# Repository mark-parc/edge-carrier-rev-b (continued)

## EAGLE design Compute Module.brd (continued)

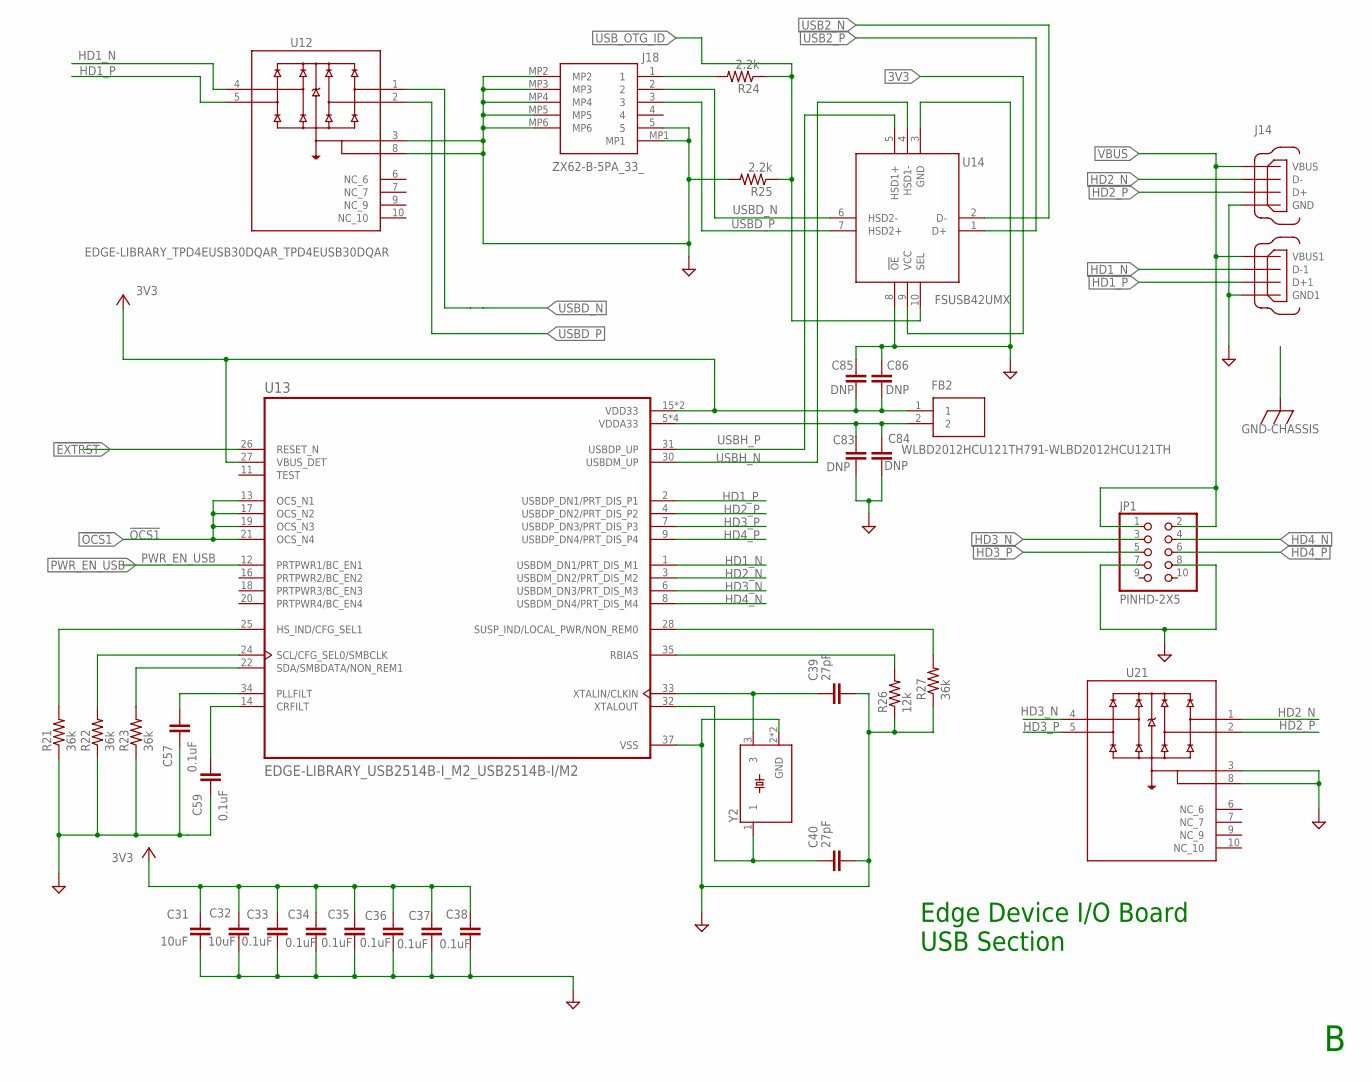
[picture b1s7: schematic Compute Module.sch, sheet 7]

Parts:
C31, C32: 10uF; EDGE-LIBRARY_TUTORIAL---FUSION-360_CAPC2012X110; MPN GRM21BR71A106KA73K; DIGIKEY 490-14381-1-ND
C33, C34, C35, C36, C37, C38, C57, C59: 0.1uF; EDGE-LIBRARY_TUTORIAL---FUSION-360_CAPC1005X60; MPN C0402C104K4RACTU; DIGIKEY 399-3521-1-ND
C39, C40: 27pF; EDGE-LIBRARY_TUTORIAL---FUSION-360_CAPC1005X60; MPN GJM1555C1H270JB01D; DIGIKEY 490-17672-1-ND
C83, C84, C85, C86: DNP; EDGE-LIBRARY_TUTORIAL---FUSION-360_CAPC1005X60; MPN C0402C104K4RACTU; DIGIKEY 399-3521-1-ND
FB2: WLBD2012HCU121TH791-WLBD2012HCU121TH; EDGE-LIBRARY_0805; MOUSER 791-WLBD2012HCU121TH
J14: EDGE-LIBRARY_USB_A_2PORT_STACKED_SMA; EDGE-LIBRARY_67298-4090_MOLEX_67298-4090
J18: ZX62-B-5PA_33_; ZX62B5PA33
JP1: PINHD-2X5; 2X05; MPN 2011-2X05G00SB; DIGIKEY 2553-2011-2X05G00SB-ND
R21, R22, R23, R27: 36k; EDGE-LIBRARY_TUTORIAL---FUSION-360_RESC1005X40; MPN RC0402FR-0736KL; DIGIKEY 311-36.0KLRCT-ND
R24, R25: 2.2k; EDGE-LIBRARY_TUTORIAL---FUSION-360_RESC1005X40; MPN RM04J222CT; DIGIKEY 2571-RM04J222CTTR-ND
R26: 12k; EDGE-LIBRARY_TUTORIAL---FUSION-360_RESC1005X40; MPN RC0402FR-0712KL; DIGIKEY 311-12.0KLRCT-ND
U12, U21: EDGE-LIBRARY_TPD4EUSB30DQAR_TPD4EUSB30DQAR; EDGE-LIBRARY_TPD4EUSB30DQAR_IC_TPD4EUSB30DQAR
U13: EDGE-LIBRARY_USB2514B-I_M2_USB2514B-I/M2; EDGE-LIBRARY_USB2514B-I_M2_QFN50P600X600X100-37N; DIGIKEY USB2514B-I/M2-ND
U14: FSUSB42UMX; QFN40P140X180X55-10N
Y2: EDGE-LIBRARY_ABM8-24.000MHZ-B2-T_ABM8-24.000MHZ-B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; EDGE-LIBRARY_ABM8-24.000MHZ-B2-T_OSCSC320X250X100N

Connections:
3V3: C31.1, C32.1, C33.1, C34.1, C35.1, C36.1, C37.1, C38.1, C85.2, C86.2, FB2.1, U13.15 (VDD33), U13.23 (VDD33), U13.27 (VBUS_DET), U14.9 (VCC); also elsewhere on the board
!EXTRST: U13.26 (RESET_N); also elsewhere on the board
!OCS1: U13.13 (OCS_N1), U13.17 (OCS_N2), U13.19 (OCS_N3), U13.21 (OCS_N4); also elsewhere on the board
GND: C31.2, C32.2, C33.2, C34.2, C35.2, C36.2, C37.2, C38.2, C39.2, C40.2, C57.1, C59.1, C83.2, C84.2, C85.1, C86.1, J14.4 (GND1), J14.8 (GND), J18.5, J18.MP1, J18.MP2, J18.MP3, J18.MP4, J18.MP5, J18.MP6, JP1.7, JP1.8, R21.1, R22.1, R23.1, R25.2, R26.1, R27.1, U12.3 (GND_3), U12.8 (GND_8), U13.37 (VSS), U14.3 (GND), U14.8 (!OE), U21.3 (GND_3), U21.8 (GND_8), Y2.2 (GND), Y2.4 (GND); also elsewhere on the board
HD1_N: J14.2 (D-1), U12.4 (D2+), U13.1 (USBDM_DN1/PRT_DIS_M1)
HD1_P: J14.3 (D+1), U12.5 (D2-), U13.2 (USBDP_DN1/PRT_DIS_P1)
HD2_N: J14.6 (D-), U13.3 (USBDM_DN2/PRT_DIS_M2), U21.1 (D1+)
HD2_P: J14.7 (D+), U13.4 (USBDP_DN2/PRT_DIS_P2), U21.2 (D1-)
HD3_N: JP1.3, U13.6 (USBDM_DN3/PRT_DIS_M3), U21.4 (D2+)
HD3_P: JP1.5, U13.7 (USBDP_DN3/PRT_DIS_P3), U21.5 (D2-)
HD4_N: JP1.4, U13.8 (USBDM_DN4/PRT_DIS_M4); also elsewhere on the board
HD4_P: JP1.6, U13.9 (USBDP_DN4/PRT_DIS_P4); also elsewhere on the board
unnamed: R23.2, U13.22 (SDA/SMBDATA/NON_REM1)
unnamed: R22.2, U13.24 (SCL/CFG_SEL0/SMBCLK)
unnamed: R21.2, U13.25 (HS_IND/CFG_SEL1)
unnamed: R27.2, U13.28 (SUSP_IND/LOCAL_PWR/NON_REM0)
unnamed: R26.2, U13.35 (RBIAS)
unnamed: C39.1, U13.33 (XTALIN/CLKIN), Y2.3
unnamed: C40.1, U13.32 (XTALOUT), Y2.1
unnamed: J18.1, R24.2
unnamed: C57.2, U13.34 (PLLFILT)
unnamed: C59.2, U13.14 (CRFILT)
unnamed: C83.1, C84.1, FB2.2, U13.5 (VDDA33), U13.10 (VDDA33), U13.29 (VDDA33), U13.36 (VDDA33)
PWR_EN_USB: U13.12 (PRTPWR1/BC_EN1); also elsewhere on the board
USB2_N: U14.2 (D-); also elsewhere on the board
USB2_P: U14.1 (D+); also elsewhere on the board
USBD_N: J18.2, U12.1 (D1+), U14.6 (HSD2-)
USBD_P: J18.3, U12.2 (D1-), U14.7 (HSD2+)
USBH_N: U13.30 (USBDM_UP), U14.4 (HSD1-)
USBH_P: U13.31 (USBDP_UP), U14.5 (HSD1+)
USB_OTG_ID: R24.1, R25.1, U14.10 (SEL); also elsewhere on the board
VBUS: J14.1 (VBUS1), J14.5 (VBUS), JP1.1, JP1.2; also elsewhere on the board

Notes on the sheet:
Edge Device I/O Board USB Section

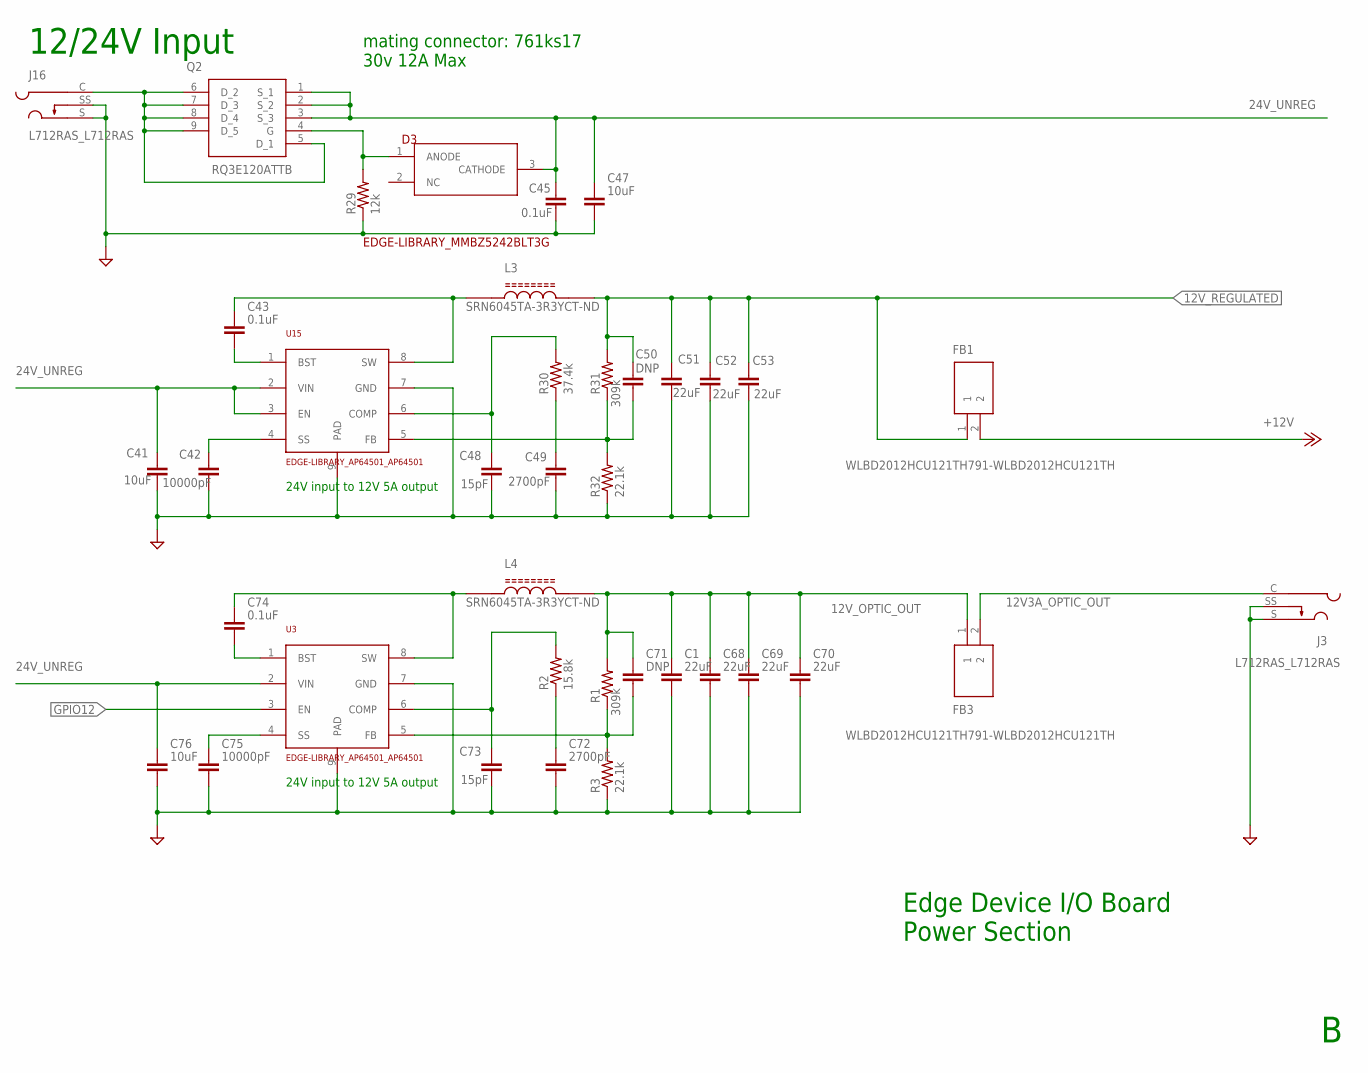
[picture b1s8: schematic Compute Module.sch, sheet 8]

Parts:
C1, C51, C52, C53, C68, C69, C70: 22uF; EDGE-LIBRARY_TUTORIAL---FUSION-360_CAPC1005X60; MPN GMC04X5R226M6R3NT; DIGIKEY 2571-GMC04X5R226M6R3NTTR-ND
C41, C47, C76: 10uF; EDGE-LIBRARY_TUTORIAL---FUSION-360_CAPC2012X110; MPN GRM21BR71A106KA73K; DIGIKEY 490-14381-1-ND
C42, C75: 10000pF; EDGE-LIBRARY_TUTORIAL---FUSION-360_CAPC1005X60; MPN CM02X5R103M16AH; DIGIKEY 1253-CM02X5R103M16AHCT-ND
C43, C45, C74: 0.1uF; EDGE-LIBRARY_TUTORIAL---FUSION-360_CAPC1005X60; MPN C0402C104K4RACTU; DIGIKEY 399-3521-1-ND
C48, C73: 15pF; EDGE-LIBRARY_TUTORIAL---FUSION-360_CAPC1005X60; MPN GMC04CG150J50NT; DIGIKEY 2571-GMC04CG150J50NTTR-ND
C49, C72: 2700pF; EDGE-LIBRARY_TUTORIAL---FUSION-360_CAPC1005X60; MPN GMC04X5R272M50NT; DIGIKEY 2571-GMC04X5R272M50NTTR-ND
C50, C71: DNP; EDGE-LIBRARY_TUTORIAL---FUSION-360_CAPC1005X60
D3: EDGE-LIBRARY_MMBZ5242BLT3G; EDGE-LIBRARY_SOT23
FB1: WLBD2012HCU121TH791-WLBD2012HCU121TH; EDGE-LIBRARY_0805; MOUSER 791-WLBD2012HCU121TH
FB3: WLBD2012HCU121TH791-WLBD2012HCU121TH; EDGE-LIBRARY_0805
J3, J16: L712RAS_L712RAS; L712RAS_SWITCHCRAFT_L712RAS; DIGIKEY SC1394-ND
L3, L4: EDGE-LIBRARY_SRN6045TA-3R3Y_SRN6045TA-3R3Y; EDGE-LIBRARY_SRN6045TA-3R3Y_IND_SRN6045TA-3R3Y
Q2: RQ3E120ATTB; RQ3E100ATTB
R1, R31: 309k; EDGE-LIBRARY_TUTORIAL---FUSION-360_RESC1005X40; MPN RM04F3093CT; DIGIKEY 2571-RM04F3093CTTR-ND
R2: 15.8k; EDGE-LIBRARY_TUTORIAL---FUSION-360_RESC1005X40; MPN CRCW040215K8FKED; DIGIKEY 541-15.8KLCT-ND
R3, R32: 22.1k; EDGE-LIBRARY_TUTORIAL---FUSION-360_RESC1005X40; MPN RN04D2212CT10-25; DIGIKEY 2571-RN04D2212CT10-25TR-ND
R29: 12k; EDGE-LIBRARY_TUTORIAL---FUSION-360_RESC1005X40; MPN RC0402FR-0712KL; DIGIKEY 311-12.0KLRCT-ND
R30: 37.4k; EDGE-LIBRARY_TUTORIAL---FUSION-360_RESC1005X40; MPN RM04F3742CT; DIGIKEY 2571-RM04F3742CTTR-ND
U3, U15: EDGE-LIBRARY_AP64501_AP64501; EDGE-LIBRARY_AP64501_SOIC127P600X265-9T261X350N

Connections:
12V3A_OPTIC_OUT: FB3.2, J3.C (CENTRE_PIN)
12V_OPTIC_OUT: C1.1, C68.1, C69.1, C70.1, C71.1, FB3.1, L4.2, R1.2; also elsewhere on the board
12V_REGULATED: C50.1, C51.1, C52.1, C53.1, FB1.1, L3.2, R31.2
24V_UNREG: C41.1, C45.1, C47.1, C76.1, D3.3 (CATHODE), Q2.1 (S_1), Q2.2 (S_2), Q2.3 (S_3), U3.2 (VIN), U15.2 (VIN), U15.3 (EN)
+12V: FB1.2; also elsewhere on the board
GND: C1.2, C41.2, C42.2, C45.2, C47.2, C48.2, C49.2, C51.2, C52.2, C53.2, C68.2, C69.2, C70.2, C72.2, C73.2, C75.2, C76.2, J3.S (SLEEVE), J3.SS (SLEEVE_SHUNT), J16.S (SLEEVE), J16.SS (SLEEVE_SHUNT), R3.1, R29.1, R32.1, U3.7 (GND), U3.9 (PAD), U15.7 (GND), U15.9 (PAD); also elsewhere on the board
GPIO12: U3.3 (EN); also elsewhere on the board
unnamed: C43.2, U15.1 (BST)
unnamed: C74.2, U3.1 (BST)
unnamed: C74.1, L4.1, U3.8 (SW)
unnamed: C75.1, U3.4 (SS)
unnamed: C73.1, R2.2, U3.6 (COMP)
unnamed: C72.1, R2.1
unnamed: C71.2, R1.1, R3.2, U3.5 (FB)
unnamed: C43.1, L3.1, U15.8 (SW)
unnamed: C42.1, U15.4 (SS)
unnamed: C48.1, R30.2, U15.6 (COMP)
unnamed: C49.1, R30.1
unnamed: C50.2, R31.1, R32.2, U15.5 (FB)
unnamed: J16.C (CENTRE_PIN), Q2.5 (D_1), Q2.6 (D_2), Q2.7 (D_3), Q2.8 (D_4), Q2.9 (D_5)
unnamed: D3.1 (ANODE), Q2.4 (G), R29.2

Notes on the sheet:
24V input to 12V 5A output
Edge Device I/O Board Power Section
mating connector: 761ks17 30v 12A Max
12/24V Input

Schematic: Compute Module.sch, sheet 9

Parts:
C54, C55: 16pF; EDGE-LIBRARY_TUTORIAL---FUSION-360_CAPC1005X60; MPN C0402C160K3HACAUTO; DIGIKEY 399-C0402C160K3HACAUTOCT-ND
C56, C60, C61, C62, C63, C65, C66, C67, C78: 0.1uF; EDGE-LIBRARY_TUTORIAL---FUSION-360_CAPC1005X60; MPN C0402C104K4RACTU; DIGIKEY 399-3521-1-ND
C64: 10uF; EDGE-LIBRARY_TUTORIAL---FUSION-360_CAPC2012X110; MPN GRM21BR71A106KA73K; DIGIKEY 490-14381-1-ND
C77, C79, C80, C82: 1uF; EDGE-LIBRARY_TUTORIAL---FUSION-360_CAPC1005X60; MPN C0402B105K016T; DIGIKEY 2873-C0402B105K016TCT-ND
C81: 22uF; EDGE-LIBRARY_TUTORIAL---FUSION-360_CAPC1005X60; MPN GMC04X5R226M6R3NT; DIGIKEY 2571-GMC04X5R226M6R3NTTR-ND
FB6: SAMACSYS_PARTS_BLM18PG121SN1D; SAMACSYS_PARTS_BLM18AG102BH1D; DIGIKEY 490-1037-1-ND
J17: EDGE-LIBRARY_L836-1J1T-43_L836-1J1T-43; EDGE-LIBRARY_L836-1J1T-43_BEL_L836-1J1T-43
L7: 3.3uH 1.5A 70m; INDPM3030X150N
R33, R40, R51, R53, R55: 10k; EDGE-LIBRARY_TUTORIAL---FUSION-360_RESC1005X40; MPN RM04J103CT; DIGIKEY 2571-RM04J103CTTR-ND
R41, R49, R50: 470; EDGE-LIBRARY_TUTORIAL---FUSION-360_RESC1005X40; MPN RC0402FR-07470RL; DIGIKEY 311-470LRCT-ND
R52: 12k; EDGE-LIBRARY_TUTORIAL---FUSION-360_RESC1005X40; MPN RC0402FR-0712KL; DIGIKEY 311-12.0KLRCT-ND
R54: 2k; EDGE-LIBRARY_TUTORIAL---FUSION-360_RESC1005X40; MPN RMCF0402JT2K00; DIGIKEY RMCF0402JT2K00CT-ND
U16: LAN7800-I_VSX; QFN40P600X600X90-49N
Y3: SAMACSYS_PARTS_ABM8G-25.000MHZ-B4Y-T3; SAMACSYS_PARTS_ABM8G48000MHZ18D2YT; DIGIKEY 535-14315-1-ND

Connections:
3V3: C63.1, C64.1, C80.1, J17.14, J17.16, R40.1, R51.1, R55.1, U16.14 (VDD_SW_IN), U16.20 (VDDVARIO_1), U16.36 (VDDVARIO_2), U16.38 (VDD33A), U16.39 (VDDVARIO_3), U16.46 (VDD25_REG_IN); also elsewhere on the board
CGND: J17.S1 (SHIELD), J17.S2 (SHIELD); also elsewhere on the board
EECLK: R49.1, U16.19 (EECLK/LED1/GPIO3); also elsewhere on the board
EECS: R33.1, U16.16 (EECS/GPIO0); also elsewhere on the board
EEDI: U16.17 (EEDI/GPIO1); also elsewhere on the board
EEDO: U16.18 (EEDO/LED0/GPIO2); also elsewhere on the board
ENET1_D0_N: J17.10 (TRD1-), U16.2 (TRON); also elsewhere on the board
ENET1_D0_P: J17.11 (TRD1+), U16.1 (TROP); also elsewhere on the board
ENET1_D1_N: J17.5 (TRD2-), U16.5 (TR1N); also elsewhere on the board
ENET1_D1_P: J17.4 (TRD2+), U16.4 (TR1P); also elsewhere on the board
ENET1_D2_N: J17.2 (TRD3-), U16.8 (TR2N); also elsewhere on the board
ENET1_D2_P: J17.3 (TRD3+), U16.7 (TR2P); also elsewhere on the board
ENET1_D3_N: J17.9 (TRD4-), U16.11 (TR3N); also elsewhere on the board
ENET1_D3_P: J17.8 (TRD4+), U16.10 (TR3P); also elsewhere on the board
GND: C54.1, C55.2, C56.2, C60.2, C61.2, C62.2, C63.2, C64.2, C65.2, C66.2, C67.2, C77.2, C78.2, C79.2, C80.2, C81.2, C82.1, R33.2, R52.2, R53.1, R54.2, U16.49 (THERMAL_PAD_(VSS)), Y3.2 (GND_1), Y3.4 (GND_2); also elsewhere on the board
HD4_N: U16.27 (USB2_DM); also elsewhere on the board
HD4_P: U16.26 (USB2_DP); also elsewhere on the board
unnamed: J17.13, R49.2
unnamed: J17.17, R50.2
unnamed: J17.15, R41.2
unnamed: R40.2, U16.23 (VBUS_DET)
unnamed: R51.2, U16.35 (RESET_N/PME_CLEAR)
unnamed: C54.2, U16.40 (XI), Y3.3 (CRYSTAL_2)
unnamed: C55.1, U16.41 (XO), Y3.1 (CRYSTAL_1)
unnamed: R52.1, U16.37 (USBRBIAS)
unnamed: R53.2, U16.34 (TEST)
unnamed: R54.1, U16.47 (REF_REXT)
unnamed: C77.1, U16.48 (REF_FILT)
unnamed: R55.2, U16.22 (PME_NGPIO4)
unnamed: C82.2, FB6.1, U16.25 (VDD12A_1)
unnamed: C62.1, J17.12 (TRCT1)
unnamed: C61.1, J17.6 (TRCT2)
unnamed: C60.1, J17.1 (TRCT3)
unnamed: C56.1, J17.7 (TRCT4)
unnamed: R50.1, U16.24 (SUSPEND_N/LED2/GPIO5)
unnamed: R41.1, U16.33 (LED3/GPIO6)
VDD12: C78.1, C81.1, FB6.2, L7.1, U16.15 (VDD12_SW_FB), U16.30 (VDD12A_2), U16.42 (VDD12CORE_2), U16.44 (VDD12A_3)
VDD12_SW_OUT: L7.2, U16.13 (VDD12_SW_OUT)
VDD25: C65.1, C66.1, C67.1, C79.1, U16.3 (VDD25A_1), U16.6 (VDD25A_2), U16.9 (VDD25A_3), U16.12 (VDD25A_4), U16.45 (VDD25_REG_OUT)

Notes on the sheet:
Edge Device I/O Board Ethernet/SD Card

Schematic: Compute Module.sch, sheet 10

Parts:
U17: SAMACSYS_PARTS_93AA66AT-I_OT; SAMACSYS_PARTS_SOT95P270X145-6N; DIGIKEY 93AA66AT-I/OTCT-ND
U18, U19: EDGE-LIBRARY_TPD4EUSB30DQAR_TPD4EUSB30DQAR; EDGE-LIBRARY_TPD4EUSB30DQAR_IC_TPD4EUSB30DQAR

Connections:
3V3: U17.6 (VCC); also elsewhere on the board
EECLK: U17.4 (CLK); also elsewhere on the board
EECS: U17.5 (CS); also elsewhere on the board
EEDI: U17.3 (DI); also elsewhere on the board
EEDO: U17.1 (DO); also elsewhere on the board
ENET1_D0_N: U18.4 (D2+); also elsewhere on the board
ENET1_D0_P: U18.5 (D2-); also elsewhere on the board
ENET1_D1_N: U18.1 (D1+); also elsewhere on the board
ENET1_D1_P: U18.2 (D1-); also elsewhere on the board
ENET1_D2_N: U19.4 (D2+); also elsewhere on the board
ENET1_D2_P: U19.5 (D2-); also elsewhere on the board
ENET1_D3_N: U19.1 (D1+); also elsewhere on the board
ENET1_D3_P: U19.2 (D1-); also elsewhere on the board
GND: U17.2 (VSS), U18.3 (GND_3), U18.8 (GND_8), U19.3 (GND_3), U19.8 (GND_8); also elsewhere on the board

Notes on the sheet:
Edge Device I/O Board Ethernet/SD Card

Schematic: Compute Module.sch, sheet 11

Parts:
C87, C88, C89, C90: 22uF; EDGE-LIBRARY_TUTORIAL---FUSION-360_CAPC1005X60; MPN GMC04X5R226M6R3NT; DIGIKEY 2571-GMC04X5R226M6R3NTTR-ND
C91: DNP; EDGE-LIBRARY_TUTORIAL---FUSION-360_CAPC1005X60
C92: 2700pF; EDGE-LIBRARY_TUTORIAL---FUSION-360_CAPC1005X60; MPN GMC04X5R272M50NT; DIGIKEY 2571-GMC04X5R272M50NTTR-ND
C93: 33pF; EDGE-LIBRARY_TUTORIAL---FUSION-360_CAPC1005X60; MPN GMC04CG330J16NT; DIGIKEY 2571-GMC04CG330J16NTTR-ND
C94: 0.1uF; EDGE-LIBRARY_TUTORIAL---FUSION-360_CAPC1005X60; MPN C0402C104K4RACTU; DIGIKEY 399-3521-1-ND
C95: 10000pF; EDGE-LIBRARY_TUTORIAL---FUSION-360_CAPC1005X60; MPN CM02X5R103M16AH; DIGIKEY 1253-CM02X5R103M16AHCT-ND
C96: 10uF; EDGE-LIBRARY_TUTORIAL---FUSION-360_CAPC2012X110; MPN GRM21BR71A106KA73K; DIGIKEY 490-14381-1-ND
L5: EDGE-LIBRARY_SRN6045TA-3R3Y_SRN6045TA-3R3Y; EDGE-LIBRARY_SRN6045TA-3R3Y_IND_SRN6045TA-3R3Y; MPN SRN6045TA-6R8M; DIGIKEY SRN6045TA-6R8MCT-ND
R28: 115k; EDGE-LIBRARY_TUTORIAL---FUSION-360_RESC1005X40; MPN RP73PF1E115KBTD; DIGIKEY A127517CT-ND
R36: 15.8k; EDGE-LIBRARY_TUTORIAL---FUSION-360_RESC1005X40; MPN CRCW040215K8FKED; DIGIKEY 541-15.8KLCT-ND
R38: 22.1k; EDGE-LIBRARY_TUTORIAL---FUSION-360_RESC1005X40; MPN RN04D2212CT10-25; DIGIKEY 2571-RN04D2212CT10-25TR-ND
U20: EDGE-LIBRARY_AP64501_AP64501; EDGE-LIBRARY_AP64501_SOIC127P600X265-9T261X350N
X1: 1751248

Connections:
5V-PELTIER: C87.1, C88.1, C89.1, C90.1, C91.1, L5.2, R28.2, X1.1
+12V: C96.1, U20.2 (VIN); also elsewhere on the board
GND: C87.2, C88.2, C89.2, C90.2, C92.2, C93.2, C95.2, C96.2, R38.1, U20.7 (GND), U20.9 (PAD), X1.2; also elsewhere on the board
GPIO05: U20.3 (EN); also elsewhere on the board
unnamed: C94.2, U20.1 (BST)
unnamed: C94.1, L5.1, U20.8 (SW)
unnamed: C95.1, U20.4 (SS)
unnamed: C93.1, R36.2, U20.6 (COMP)
unnamed: C92.1, R36.1
unnamed: C91.2, R28.1, R38.2, U20.5 (FB)

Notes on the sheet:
Edge Device I/O Board Peltier Driver
12V input to 5V 3A output

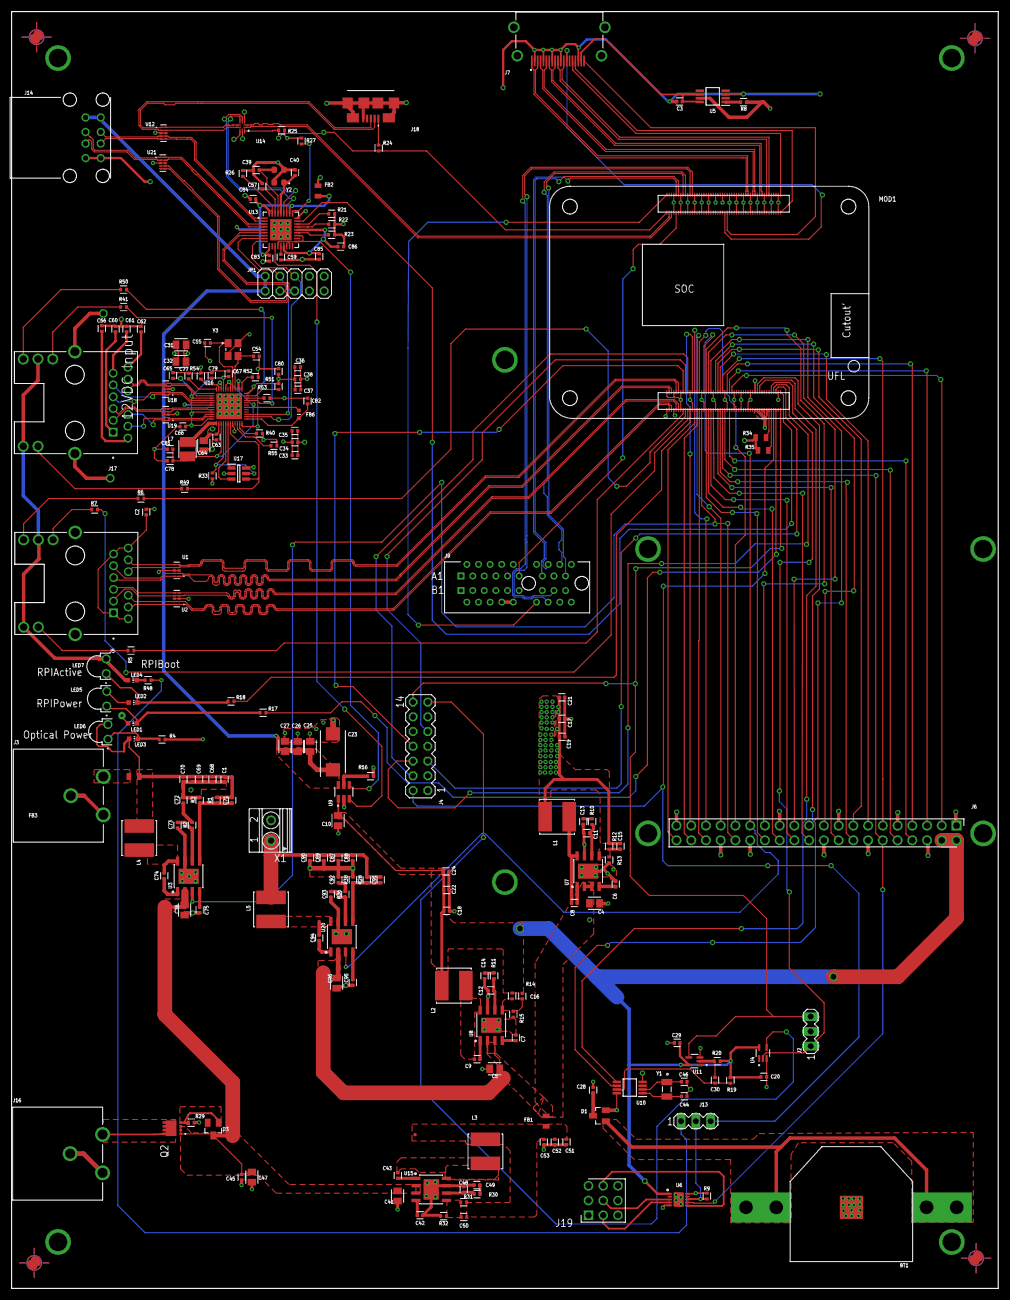
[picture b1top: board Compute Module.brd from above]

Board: 4 copper layers, 170.0 x 220.0 mm, 217 parts (0 on the bottom side), 203 nets.

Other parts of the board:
U$1, U$3, U$4, U$8: PASS-ROUND

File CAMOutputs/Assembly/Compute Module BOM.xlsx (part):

Qty | Parts | Value | Description | DIGIKEY | MANUFACTURER | MOUSER | MPN | Device
2 | R34, R35 |  | Generic Resistor Package | 311-0.0ARCT-ND |  |  | RC0805JR-070RL | EDGE-LIBRARY_RESISTOR0805
28 | C2, C3, C8, C9, C28, C29, C30, C33, C34, C35, C36, C37, C38, C43, C45, C56, C57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 | 0.1uF | Capacitor - Generic | 399-3521-1-ND | Kemet |  | C0402C104K4RACTU | EDGE-LIBRARY_TUTORIAL---FUSION-360_CCHIP-0402(1005-METRIC)
1 | R10 | 10.5k | Resistor Fixed - ANSI | YAG2951CT-ND | Yageo |  | RC0402FR-0710K5L | EDGE-LIBRARY_TUTORIAL---FUSION-360_R-USCHIP-0402(1005-METRIC)
5 | C6, C7, C42, C75, C95 | 10000pF | Capacitor - Generic | 1253-CM02X5R103M16AHCT-ND | AVX Corporation |  | CM02X5R103M16AH | EDGE-LIBRARY_TUTORIAL---FUSION-360_CCHIP-0402(1005-METRIC)
1 | C23 | 100uF | Wurth Elektronik 100uF 6.3V dc Aluminium Polymer Capacitor, Surface Mount 7.3 x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 | 732-13327-1-nd | Wurth Elektronik | 710-875015119003 | 875015119003 | 875015119003
6 | R9, R33, R40, R51, R53, R55 | 10k | Resistor Fixed - ANSI | 2571-RM04J103CTTR-ND | CAL-CHIP ELECTRONICS, INC. |  | RM04J103CT | EDGE-LIBRARY_TUTORIAL---FUSION-360_R-USCHIP-0402(1005-METRIC)
1 | C44 | 10pF | Capacitor - Generic | 399-3521-1-ND | Kyocera Avx |  | 478-04026D100JAT2ACT-ND | EDGE-LIBRARY_TUTORIAL---FUSION-360_CCHIP-0402(1005-METRIC)
13 | C4, C5, C10, C25, C26, C27, C31, C32, C41, C47, C64, C76, C96 | 10uF | Capacitor - Generic | 490-14381-1-ND | Murata Electronics |  | GRM21BR71A106KA73K | EDGE-LIBRARY_TUTORIAL---FUSION-360_CCHIP-0402(1005-METRIC)
2 | R14, R28 | 115k | Resistor Fixed - ANSI | A127517CT-ND | TE Connectivity |  | RP73PF1E115KBTD | EDGE-LIBRARY_TUTORIAL---FUSION-360_R-USCHIP-0402(1005-METRIC)
1 | R52 | 12k | Resistor Fixed - ANSI | 311-12.0KLRCT-ND | Stackpole Electronics Inc |  | RC0402FR-0712KL | EDGE-LIBRARY_TUTORIAL---FUSION-360_R-USCHIP-0402(1005-METRIC)
3 | R8, R26, R29 | 12k | Resistor Fixed - ANSI | 311-12.0KLRCT-ND | Yageo |  | RC0402FR-0712KL | EDGE-LIBRARY_TUTORIAL---FUSION-360_R-USCHIP-0402(1005-METRIC)
1 | C46 | 12pF | Capacitor - Generic | 478-04026A120KAT2ACT-ND | Kyocera Avx |  | 04026A120KAT2A | EDGE-LIBRARY_TUTORIAL---FUSION-360_CCHIP-0402(1005-METRIC)
3 | R2, R11, R36 | 15.8k | Resistor Fixed - ANSI | 541-15.8KLCT-ND | Vishay Dale |  | CRCW040215K8FKED | EDGE-LIBRARY_TUTORIAL---FUSION-360_R-USCHIP-0402(1005-METRIC)
1 | R16 | 15k | Resistor Fixed - ANSI | RMCF0402FT15K0CT-ND | Stackpole Electronics Inc |  | RMCF0402FT15K0 | EDGE-LIBRARY_TUTORIAL---FUSION-360_R-USCHIP-0402(1005-METRIC)
2 | C48, C73 | 15pF | Capacitor - Generic | 2571-GMC04CG150J50NTTR-ND | CAL-CHIP ELECTRONICS, INC. |  | GMC04CG150J50NT | EDGE-LIBRARY_TUTORIAL---FUSION-360_CCHIP-0402(1005-METRIC)
2 | C54, C55 | 16pF | Capacitor - Generic | 399-C0402C160K3HACAUTOCT-ND | Kemet |  | C0402C160K3HACAUTO | EDGE-LIBRARY_TUTORIAL---FUSION-360_CCHIP-0402(1005-METRIC)
1 | X1 | 1751248 | MKDS 1/ 2-3,5 Printklemme |  |  |  |  | 1751248
4 | C77, C79, C80, C82 | 1uF | Capacitor - Generic | 2873-C0402B105K016TCT-ND | Holy Stone Enterprise Co., Ltd. |  | C0402B105K016T | EDGE-LIBRARY_TUTORIAL---FUSION-360_CCHIP-0402(1005-METRIC)
2 | R24, R25 | 2.2k | Resistor Fixed - ANSI | 2571-RM04J222CTTR-ND | CAL-CHIP ELECTRONICS, INC. |  | RM04J222CT | EDGE-LIBRARY_TUTORIAL---FUSION-360_R-USCHIP-0402(1005-METRIC)
1 | J2 | 2011-1X03G00SD025B | PIN HEADER | 2553-2011-1X03G00SB-ND | Oupiin |  | 2011-1X03G00SB | CON-LSTB_MA03-1
1 | J4 | 2011-2X07G00SB | PIN HEADER | 2553-2011-2X07G00SB-ND | Oupiin |  | 2011-2X07G00SB | CON-LSTB_MA07-2
4 | R3, R15, R32, R38 | 22.1k | Resistor Fixed - ANSI | 2571-RN04D2212CT10-25TR-ND | CAL-CHIP ELECTRONICS, INC. |  | RN04D2212CT10-25 | EDGE-LIBRARY_TUTORIAL---FUSION-360_R-USCHIP-0402(1005-METRIC)
1 | R13 | 22k | Resistor Fixed - ANSI | 2571-RM04J222CTTR-ND | CAL-CHIP ELECTRONICS, INC. |  | RM04J223CT | EDGE-LIBRARY_TUTORIAL---FUSION-360_R-USCHIP-0402(1005-METRIC)
19 | C1, C17, C18, C19, C20, C21, C22, C24, C51, C52, C53, C68, C69, C70, C81, C87, 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 | 22uF | Capacitor - Generic | 2571-GMC04X5R226M6R3NTTR-ND | CAL-CHIP ELECTRONICS, INC. |  | GMC04X5R226M6R3NT | EDGE-LIBRARY_TUTORIAL---FUSION-360_CCHIP-0402(1005-METRIC)
1 | J13 | 2553-2011-1X03G00SB-ND | PIN HEADER | 2553-2011-1X03G00SB-ND | Oupiin |  | 2011-1X03G00SB | CON-LSTB_MA03-1
5 | C13, C14, C49, C72, C92 | 2700pF | Capacitor - Generic | 2571-GMC04X5R272M50NTTR-ND | CAL-CHIP ELECTRONICS, INC. |  | GMC04X5R272M50NT | EDGE-LIBRARY_TUTORIAL---FUSION-360_CCHIP-0402(1005-METRIC)
2 | C39, C40 | 27pF | Capacitor - Generic | 490-17672-1-ND | Murata Electronics |  | GJM1555C1H270JB01D | EDGE-LIBRARY_TUTORIAL---FUSION-360_CCHIP-0402(1005-METRIC)
1 | R54 | 2k | Resistor Fixed - ANSI | RMCF0402JT2K00CT-ND | Stackpole Electronics Inc |  | RMCF0402JT2K00 | EDGE-LIBRARY_TUTORIAL---FUSION-360_R-USCHIP-0402(1005-METRIC)
1 | L7 | 3.3uH 1.5A 70m | SMT Power Inductor | 732-5494-1-ND | Wurth Elektronik |  | 74404032033 | 74404032033
2 | R1, R31 | 309k | Resistor Fixed - ANSI | 2571-RM04F3093CTTR-ND | CAL-CHIP ELECTRONICS, INC. |  | RM04F3093CT | EDGE-LIBRARY_TUTORIAL---FUSION-360_R-USCHIP-0402(1005-METRIC)
1 | D1 | 30V 200MA | Schottky Diodes | BAT54C-FDICT-ND | Diodes Incorporated |  | BAT54C-7-F | EDGE-LIBRARY_BAT54C
2 | C12, C93 | 33pF | Capacitor - Generic | 2571-GMC04CG330J16NTTR-ND | CAL-CHIP ELECTRONICS, INC. |  | GMC04CG330J16NT | EDGE-LIBRARY_TUTORIAL---FUSION-360_CCHIP-0402(1005-METRIC)
4 | R21, R22, R23, R27 | 36k | Resistor Fixed - ANSI | 311-36.0KLRCT-ND | Yageo |  | RC0402FR-0736KL | EDGE-LIBRARY_TUTORIAL---FUSION-360_R-USCHIP-0402(1005-METRIC)
1 | R30 | 37.4k | Resistor Fixed - ANSI | 2571-RM04F3742CTTR-ND | CAL-CHIP ELECTRONICS, INC. |  | RM04F3742CT | EDGE-LIBRARY_TUTORIAL---FUSION-360_R-USCHIP-0402(1005-METRIC)
10 | R4, R5, R6, R7, R17, R18, R41, R48, R49, R50 | 470 | Resistor Fixed - ANSI | 311-470LRCT-ND | Yageo |  | RC0402FR-07470RL | EDGE-LIBRARY_TUTORIAL---FUSION-360_R-USCHIP-0402(1005-METRIC)
2 | R19, R20 | 510k | Resistor Fixed - ANSI | RMCF0402JT510KCT-ND | Stackpole Electronics Inc |  | RMCF0402JT510K | EDGE-LIBRARY_TUTORIAL---FUSION-360_R-USCHIP-0402(1005-METRIC)
1 | C11 | 56pF | Capacitor - Generic | 587-6134-1-ND | Taiyo Yuden |  | EMK042CG560JC-W | EDGE-LIBRARY_TUTORIAL---FUSION-360_CCHIP-0402(1005-METRIC)
1 | J6 | 67996-140HLF | AMPHENOL ICC (FCI) - 67996-140HLF - CONNECTOR, HEADER, 40POS, 2ROW, 2.54MM | 609-4925-ND | Amphenol | 649-67996-140HLF | 67996-140HLF | 67996-140HLF
1 | R12 | 69.8k | Resistor Fixed - ANSI | RMCF0402FT69K8CT-ND | Stackpole Electronics Inc |  | RMCF0402FT69K8 | EDGE-LIBRARY_TUTORIAL---FUSION-360_R-USCHIP-0402(1005-METRIC)
4 | C83, C84, C85, C86 | DNP | Capacitor - Generic | 399-3521-1-ND | Kemet |  | C0402C104K4RACTU | EDGE-LIBRARY_TUTORIAL---FUSION-360_CCHIP-0402(1005-METRIC)
5 | C15, C16, C50, C71, C91 | DNP | Capacitor - Generic |  |  |  |  | EDGE-LIBRARY_TUTORIAL---FUSION-360_CCHIP-0402(1005-METRIC)
2 | U4, U11 | EDGE-LIBRARY_74LVC1G07SE-7 | Check prices | 74LVC1G07SE-7DICT-ND | Diodes Inc |  | 74LVC1G07SE-7 | EDGE-LIBRARY_74LVC1G07SE-7
1 | Y2 | EDGE-LIBRARY_ABM8-24.000MHZ-B2-T_ABM8-24.000MHZ-B2-T | Crystal 24MHz Â±20ppm (Tol) Â±30ppm (Stability) 18pF FUND 80Ohm 4-Pin Mini-CSMD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 | 535-9138-1-ND | Abracon |  | ABM8-24.000MHZ-B2-T | EDGE-LIBRARY_ABM8-24.000MHZ-B2-T_ABM8-24.000MHZ-B2-T
1 | U9 | EDGE-LIBRARY_AP2553AW6-7 |  | 31-AP22653AW6-7CT-ND | Diodes Incorporated |  | AP22653AW6-7 | EDGE-LIBRARY_AP2553AW6-7
5 | U3, U7, U8, U15, U20 | EDGE-LIBRARY_AP64501_AP64501 |  | AP64501SP-13CT-ND | Diodes Incorporated |  | AP64501SP-13 | EDGE-LIBRARY_AP64501_AP64501
1 | BT1 | EDGE-LIBRARY_BATTERY_HOLDER | BATTERY RETAINER COIN 20MM SMD | 732-12323-2-ND | Wurth Electronics Inc. |  | 79523141 | EDGE-LIBRARY_BATTERY_HOLDER
1 | J7 | EDGE-LIBRARY_HDMI_CONNECTOR_RT_SMA | HDMI Connector | Right Angle | Without Flange | -20C to 85C | 380-SS-53000-001-ND | Stewart Connector |  | SS-53000-001 | EDGE-LIBRARY_HDMI_CONNECTOR_RT_SMA
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
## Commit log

2022-02-08 Edge Carrier Rev B Schematics and PCB files
2022-02-18 Added gerbers
